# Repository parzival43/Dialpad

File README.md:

# Dialpad — Custom Macropad

A custom-designed macropad built around the **Seeed Studio XIAO RP2040**, featuring 12 mechanical keys, two rotary controls, a joystick, and a display. Designed with KiCad and Fusion 360, Dialpad brings everything a normal keyboard misses! even a joystick!
Specifically made to optimize cad designing experience and improve player control in video games.  

### Features

- **12 mechanical keys** for shortcuts and custom actions
- **Resistor ladder wiring method** allows multiple keys to share a single analog gpio
- **2 rotary controls** for adjustable parameters and navigation
- **1 joystick** for directional input
- **Display** for visual feedback
- **XIAO RP2040** as the main microcontroller
- Custom PCB designed in KiCad
- Custom enclosure designed in Fusion 360
- Custom micropython firmware with serial communicaiton

## Project Gallery

### 1. Complete Macropad

### 2. Schematic

### 3. PCB Layout

<!-- Add a screenshot of the PCB layout exported from KiCad. -->

### 4. Case Design and Assembly

<!-- Add a Fusion 360 screenshot showing the assembled case and how its parts fit together. -->

## Bill of Materials (BOM)

| Component | Quantity | Purpose |
|---|---:|---|
| Seeed Studio XIAO RP2040 | 1 | Main microcontroller |
| Mechanical key switches | 12 | Primary key inputs |
| Rotary encoders | 2 | Rotary input and adjustment |
| Joystick module | 1 | Directional input |
| Display module | 1 | Visual feedback |
| PCB | 1 | Main circuit board |
| Resistors | 17 | Input circuitry |
| Diodes | 17 | Input circuitry |
| USB cable | 1 | Power and USB connection |
| 3D-printed enclosure | 1 set | Protects and supports the electronics |
| Keycaps | 12 | Key tops |
| Knobs | 2 | Rotary encoder controls |
| Heatset brass inserts | 3 | Secures the PCB and enclosure |
| M3 Screws | 3 | Secures the PCB and enclosure |

## Repository Structure

```text
Dialpad/
├── CAD/
│   └── Complete case assembly (STEP/STP/3MF)
├── PCB/
│   ├── KiCad project file (.kicad_pro)
│   ├── Schematic file (.kicad_sch)
│   └── PCB layout file (.kicad_pcb)
├── Firmware/
│   └── Firmware source files
├── production/
│   ├── gerbers.zip
│   ├── Case manufacturing files (STEP/STL)
│   └── Firmware build (if applicable)
├── assets/
│   ├── pcb_layout.png
│   └── case_assembly.png
├── dialpad.png
├── Kicad_schematic_photo.png
└── README.md
```

## Design Tools

- **KiCad** — schematic capture and PCB design
- **Fusion 360** — enclosure design and CAD assembly
- **MicroPython** — firmware development, if using the current MicroPython implementation

## Project Status

- The PCB design, and the enclosure and firmware have been developed.
- Basic v1 firmware complete.
- Working on backend

## Acknowledgements

Created as part of the Hackpad project by Hack Club.

---

**Repository:** [parzival43/Dialpad](https://github.com/parzival43/Dialpad)

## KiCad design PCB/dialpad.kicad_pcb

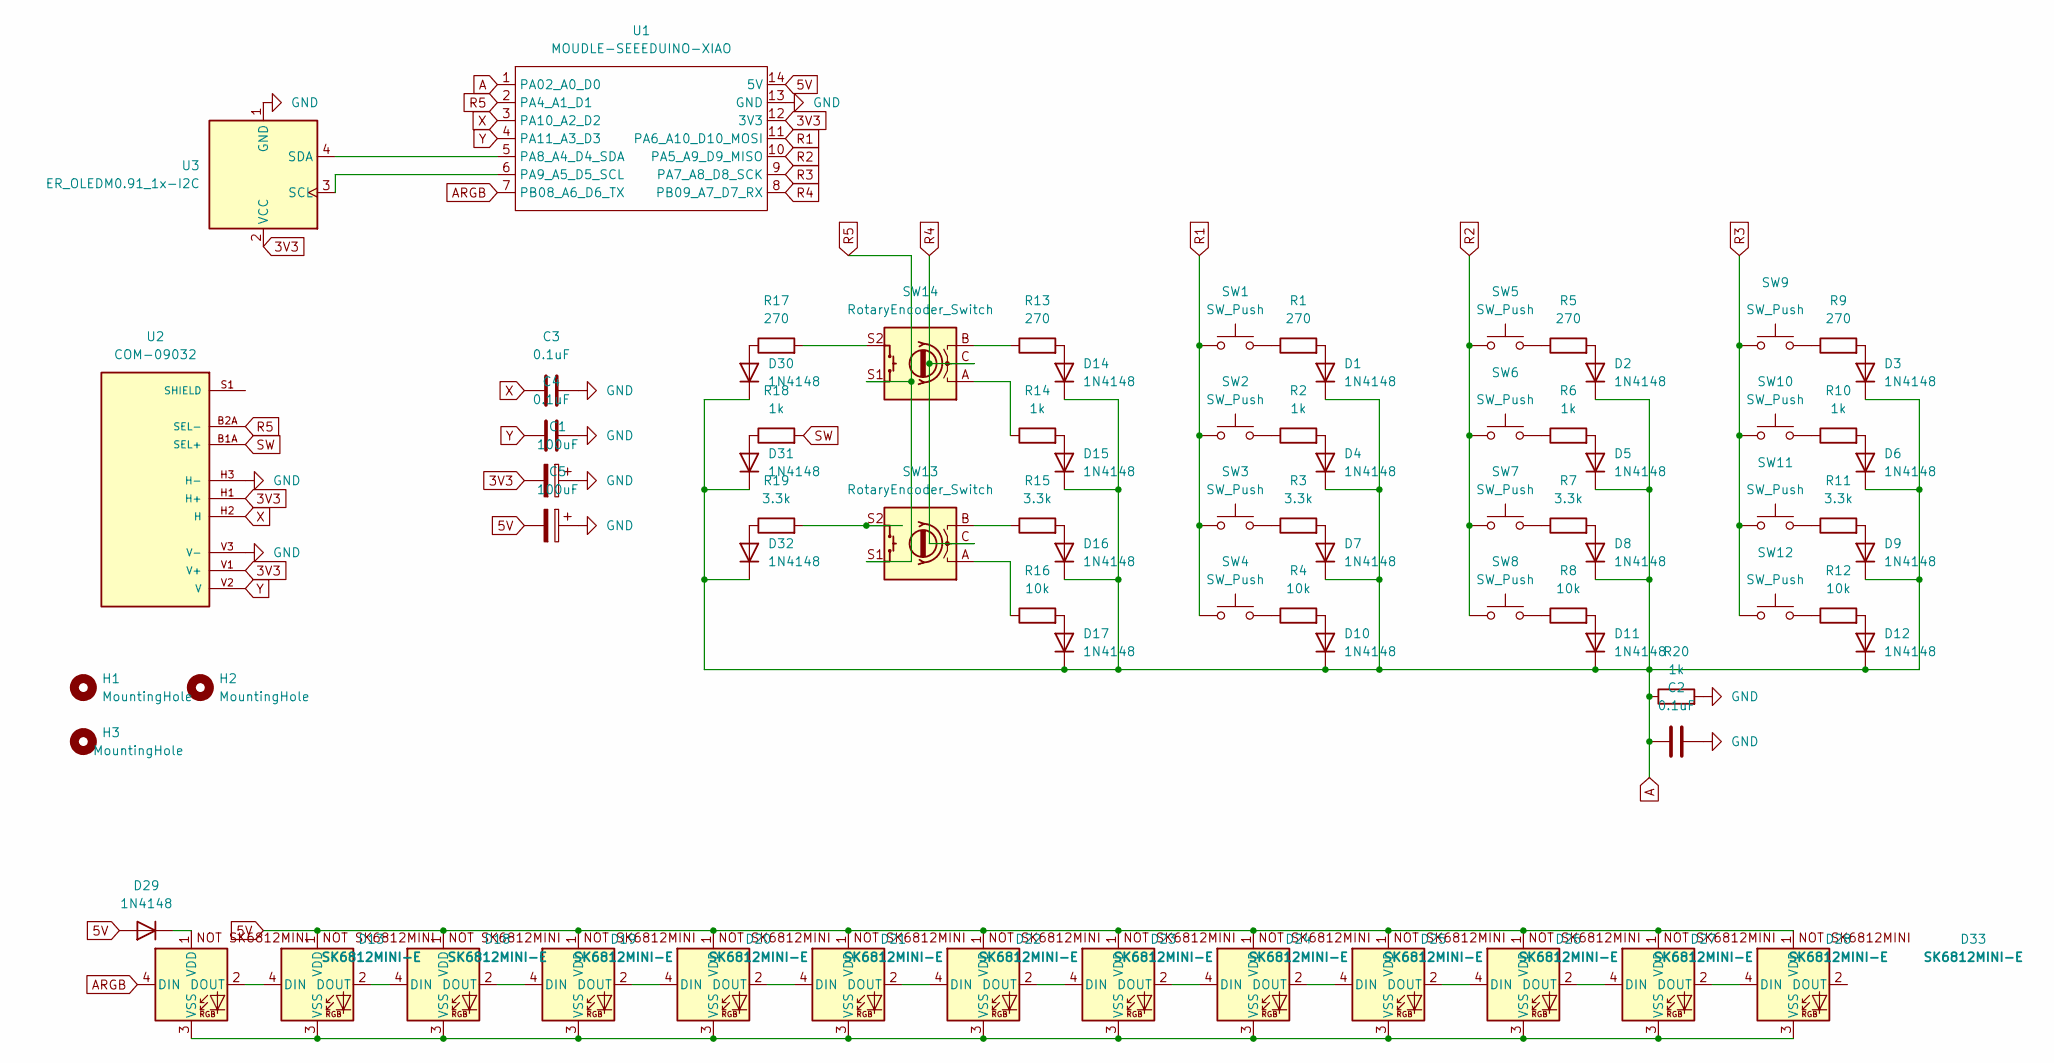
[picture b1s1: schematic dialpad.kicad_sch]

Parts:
C1, C5: 100uF; CP_Radial_D6.3mm_P2.50mm
C2, C3, C4: 0.1uF; C_Disc_D5.0mm_W2.5mm_P5.00mm
D1, D2, D3, D4, D5, D6, D7, D8, D9, D10, D11, D12, D14, D15, D16, D17, D29, D30, D31, D32: 1N4148; D_DO-35_SOD27_P7.62mm_Horizontal
D13, D18, D19, D20, D21, D22, D23, D24, D25, D26, D27, D28, D33: SK6812MINI-E; SK6812MINI-E_fixed
H1, H2, H3: MountingHole; MountingHole_3.2mm_M3_Pad
R1, R5, R9, R13, R17: 270; R_Axial_DIN0207_L6.3mm_D2.5mm_P7.62mm_Horizontal
R2, R6, R10, R14, R18, R20: 1k; R_Axial_DIN0207_L6.3mm_D2.5mm_P7.62mm_Horizontal
R3, R7, R11, R15, R19: 3.3k; R_Axial_DIN0207_L6.3mm_D2.5mm_P7.62mm_Horizontal
R4, R8, R12, R16: 10k; R_Axial_DIN0207_L6.3mm_D2.5mm_P7.62mm_Horizontal
SW1, SW2, SW3, SW4, SW5, SW6, SW7, SW8, SW9, SW10, SW11, SW12: SW_Push; SW_Cherry_MX_1.00u_PCB
SW13, SW14: RotaryEncoder_Switch; RotaryEncoder_Alps_EC11E-Switch_Vertical_H20mm
U1: MOUDLE-SEEEDUINO-XIAO; XIAO-Generic-Hybrid-14P-2.54-21X17.8MM
U2: COM-09032; XDCR_COM-09032; PARTREV N/A
U3: ER_OLEDM0.91_1x-I2C

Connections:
3V3: C1.2, U1.12 (3V3), U2.H1 (H+), U2.V1 (V+), U3.2 (VCC)
5V: C5.2, D18.1 (VDD), D19.1 (VDD), D20.1 (VDD), D21.1 (VDD), D22.1 (VDD), D23.1 (VDD), D24.1 (VDD), D25.1 (VDD), D26.1 (VDD), D27.1 (VDD), D28.1 (VDD), D29.2 (A), D33.1 (VDD), U1.14 (5V)
A: C2.1, D1.1 (K), D2.1 (K), D3.1 (K), D4.1 (K), D5.1 (K), D6.1 (K), D7.1 (K), D8.1 (K), D9.1 (K), D10.1 (K), D11.1 (K), D12.1 (K), D14.1 (K), D15.1 (K), D16.1 (K), D17.1 (K), D30.1 (K), D31.1 (K), D32.1 (K), R20.1, U1.1 (PA02_A0_D0)
ARGB: D13.4 (DIN), U1.7 (PB08_A6_D6_TX)
GND: C1.1, C2.2, C3.2, C4.2, C5.1, R20.2, U1.13 (GND), U2.H3 (H-), U2.V3 (V-), U3.1 (GND)
unnamed: D1.2 (A), R1.2
unnamed: D2.2 (A), R5.2
unnamed: D3.2 (A), R9.2
unnamed: D4.2 (A), R2.2
unnamed: D5.2 (A), R6.2
unnamed: D6.2 (A), R10.2
unnamed: D7.2 (A), R3.2
unnamed: D8.2 (A), R7.2
unnamed: D9.2 (A), R11.2
unnamed: D10.2 (A), R4.2
unnamed: D11.2 (A), R8.2
unnamed: D12.2 (A), R12.2
unnamed: D13.2 (DOUT), D18.4 (DIN)
unnamed: D13.1 (VDD), D29.1 (K)
unnamed: D13.3 (VSS), D18.3 (VSS), D19.3 (VSS), D20.3 (VSS), D21.3 (VSS), D22.3 (VSS), D23.3 (VSS), D24.3 (VSS), D25.3 (VSS), D26.3 (VSS), D27.3 (VSS), D28.3 (VSS), D33.3 (VSS)
unnamed: D14.2 (A), R13.2
unnamed: D15.2 (A), R14.2
unnamed: D16.2 (A), R15.2
unnamed: D17.2 (A), R16.2
unnamed: D18.2 (DOUT), D19.4 (DIN)
unnamed: D19.2 (DOUT), D20.4 (DIN)
unnamed: D20.2 (DOUT), D21.4 (DIN)
unnamed: D21.2 (DOUT), D22.4 (DIN)
unnamed: D22.2 (DOUT), D23.4 (DIN)
unnamed: D23.2 (DOUT), D24.4 (DIN)
unnamed: D24.2 (DOUT), D25.4 (DIN)
unnamed: D25.2 (DOUT), D26.4 (DIN)
unnamed: D26.2 (DOUT), D27.4 (DIN)
unnamed: D27.2 (DOUT), D28.4 (DIN)
unnamed: D28.2 (DOUT), D33.4 (DIN)
unnamed: D30.2 (A), R17.1
unnamed: D31.2 (A), R18.1
unnamed: D32.2 (A), R19.1
unnamed: R1.1, SW1.2
unnamed: R2.1, SW2.2
unnamed: R3.1, SW3.2
unnamed: R4.1, SW4.2
unnamed: R5.1, SW5.2
unnamed: R6.1, SW6.2
unnamed: R7.1, SW7.2
unnamed: R8.1, SW8.2
unnamed: R9.1, SW9.2
unnamed: R10.1, SW10.2
unnamed: R11.1, SW11.2
unnamed: R12.1, SW12.2
unnamed: R13.1, SW14.B
unnamed: R14.1, SW14.A
unnamed: R15.1, SW13.B
unnamed: R16.1, SW13.A
unnamed: R17.2, SW14.S2
unnamed: R19.2, SW13.S2
unnamed: U1.5 (PA8_A4_D4_SDA), U3.4 (SDA)
unnamed: U1.6 (PA9_A5_D5_SCL), U3.3 (SCL)
unnamed: U2.S1 (SHIELD), U2.S2 (SHIELD), U2.S3 (SHIELD), U2.S4 (SHIELD)
R1: SW1.1, SW2.1, SW3.1, SW4.1, U1.11 (PA6_A10_D10_MOSI)
R2: SW5.1, SW6.1, SW7.1, SW8.1, U1.10 (PA5_A9_D9_MISO)
R3: SW9.1, SW10.1, SW11.1, SW12.1, U1.9 (PA7_A8_D8_SCK)
R4: SW13.C, SW14.C, U1.8 (PB09_A7_D7_RX)
R5: SW13.S1, SW14.S1, U1.2 (PA4_A1_D1), U2.B2A (SEL-)
SW: R18.2, U2.B1A (SEL+)
X: C3.1, U1.3 (PA10_A2_D2), U2.H2 (H)
Y: C4.1, U1.4 (PA11_A3_D3), U2.V2 (V)

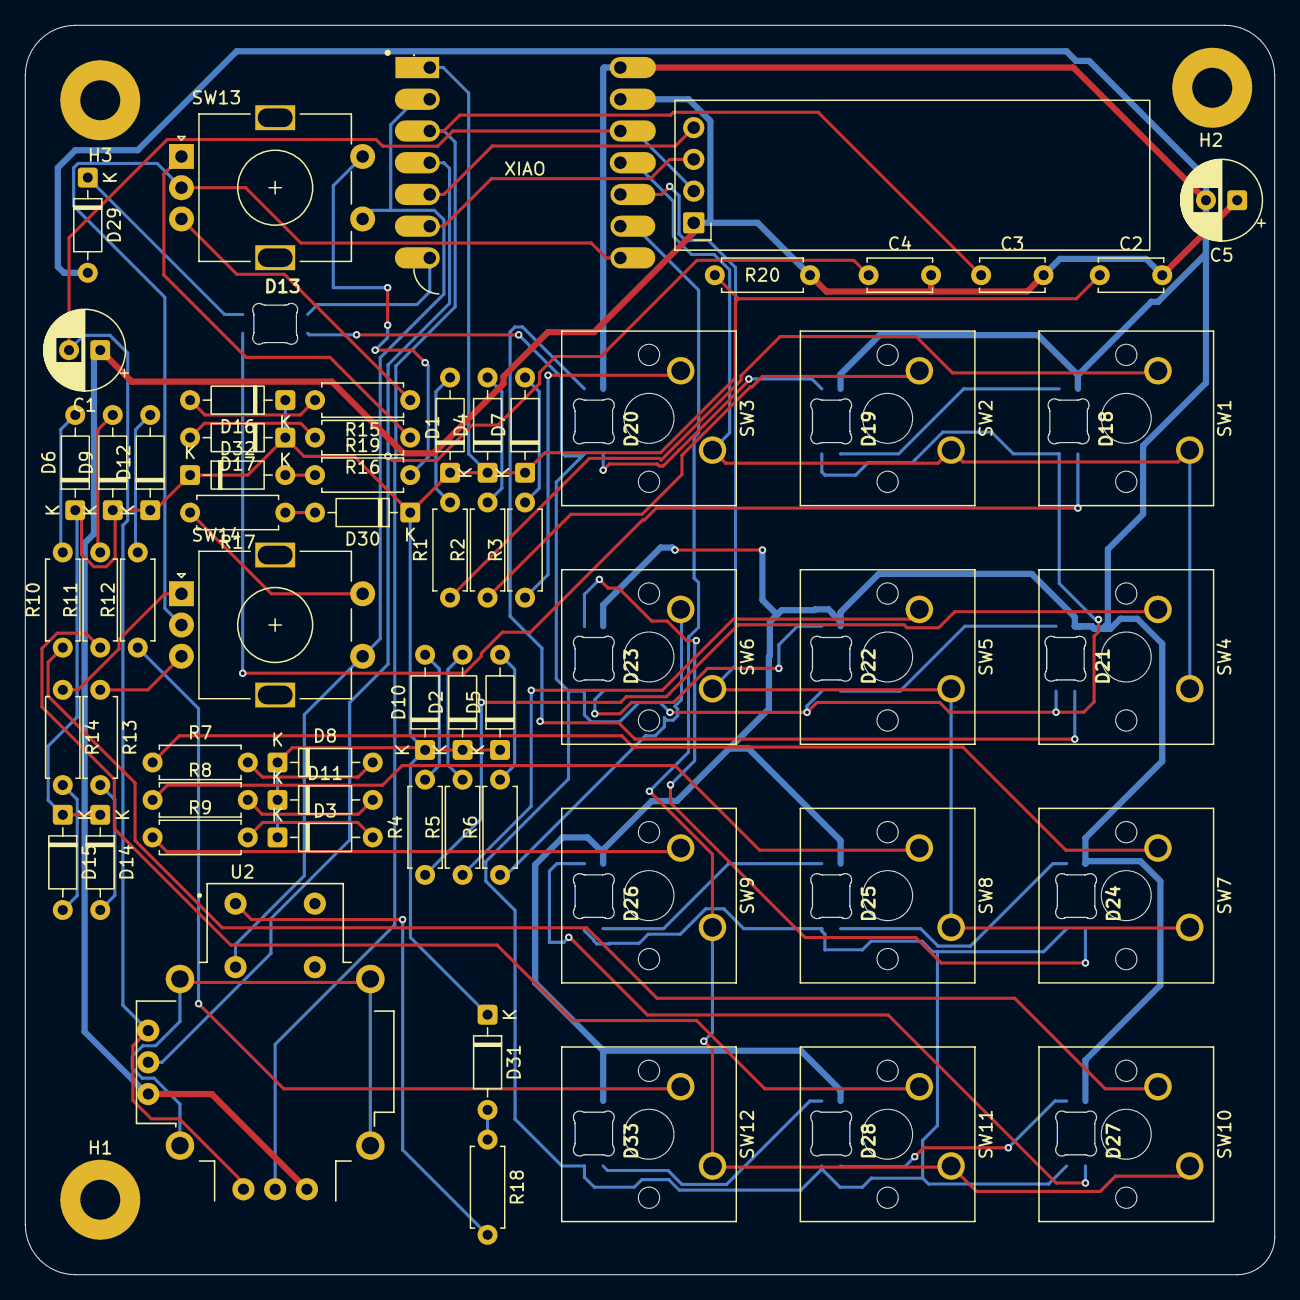
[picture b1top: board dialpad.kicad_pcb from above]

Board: 2 copper layers, 100.0 x 100.0 mm, 78 parts (0 on the bottom side), 67 nets.
